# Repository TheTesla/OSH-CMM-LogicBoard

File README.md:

# Coordinate Measurement Arm Logic Board

This logic board implements the main functionality of the 5-dof coordinate measurement arm. The central component is an _Arduino UNO R3_. It reads the rotary encoders out and provides the communication to the host PC and power supply via the USB port. 

The 5 rotary encoders are plugged into the D-Sub-9 socket. The board implements electrical protection circuits, that the _Arduino_ won't be damaged, if voltage is accidentally applied to the encoder connectors. Unfortunatelly, the  USB port can't be protected, because it is directly part of the _Aduino_.

The board also boosts the power supply voltage from the USB port to operate the rotary encoders.

## Implementation

The rotary encoders are powered by a 5 V to 9 V voltage converter, because they need at least 5 V. This lower limit is not maintained by the USB port, which can deliver down to 4.75 V.

Diodes protect the board from excessive positive voltage from the encoder connectors, while 3 transistors protect it from short circuit and negative voltage levels on the encoder supply line. The shunt _R14_ sets the current limit to around 300 mA. At this cuurent level, the b-e-voltage of _Q2_ reaches 660 mV. IN this case _Q2_ starts to disable the output transistor _Q1_. If the output voltage drops down to around 0 V, the diode _D7_ switches the transistor _Q3_ off and so also _Q1_. This reduces the output current in case of short circuit or reverse polarity voltage injection into the power supply output. Diode _D1_ protects _Q3_ against reverse voltage on the output line. 

The _Arduino_ is able to measure the output voltage to report short circuit conditions also as a self test for production end test. 

The encoder data lines are connected via 10k resistors to the _Arduino_ to protect the inputs against excessive voltage from the encoder connector.

The open collector outputs of the encoders need pull-up resistors. These are integrated into the plug of the encoder itself.

If the board is powered up, the power on indicator LED _D10_ shows the correct operation of the voltage converter. If the power supply for the rotary encoders is on, LED _D8_ lights up. For debugging and error indication, the LED _D9_ can be activated by the _Arduino_.

## Associated Projects

The rotary encoders are shipped with open wire ends. A plug has to be attached to this cable. Because there is no electrical protection in the encoder itself. it should be integrated in the plug. This project implements the protection circuit:

* https://github.com/TheTesla/rotary-encoder-protection

## Author/Contact

Stefan Helmert <stefan.helmert@htw-dresden.de>

## Appendix

### Pictures

The following pictures show the rendering of the assembled pcb. The arduino board is not available as 3d model.

### Schematics

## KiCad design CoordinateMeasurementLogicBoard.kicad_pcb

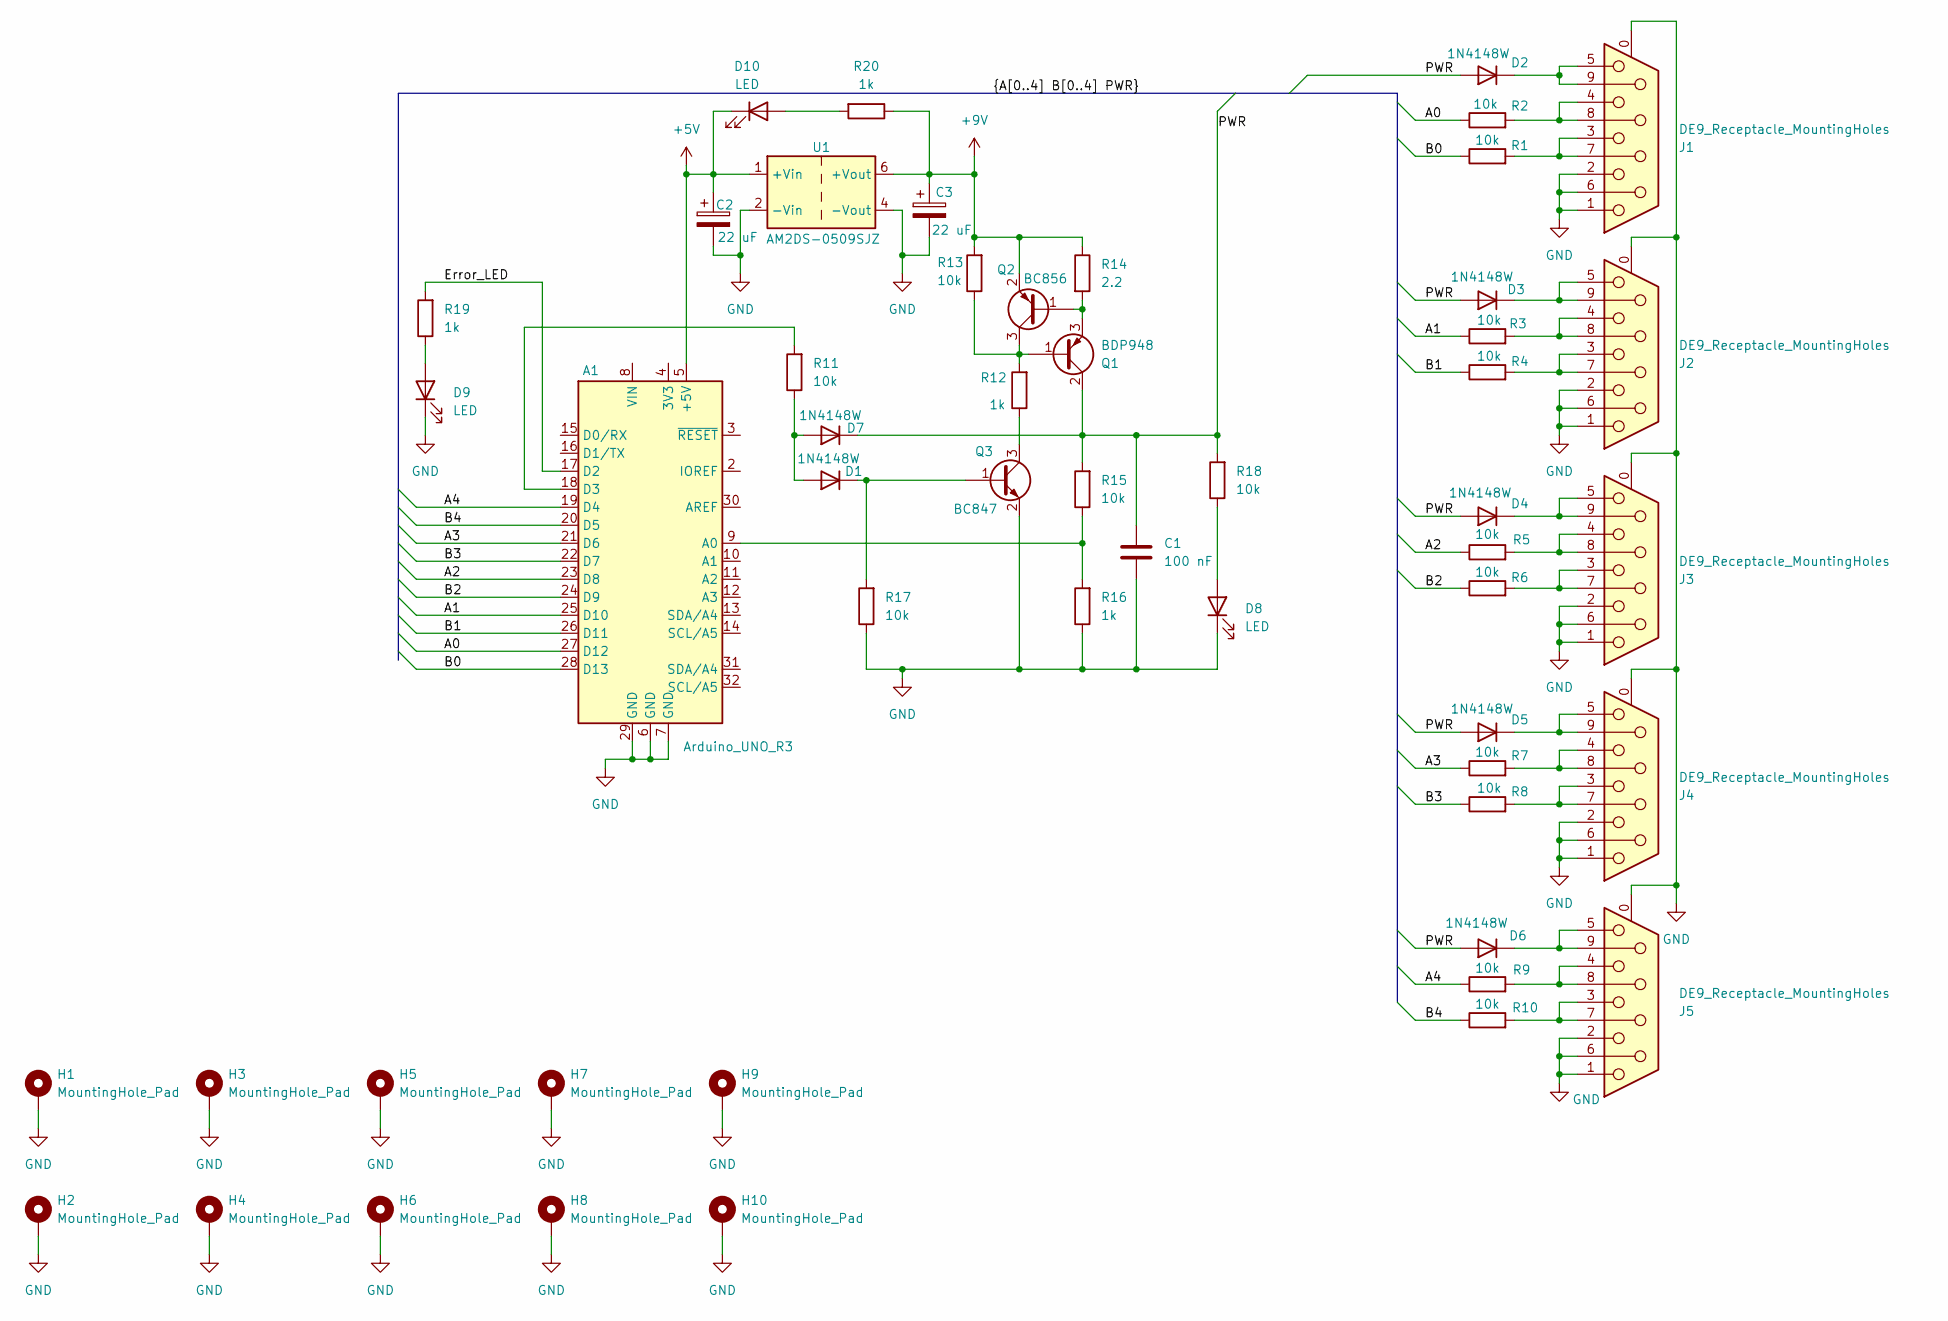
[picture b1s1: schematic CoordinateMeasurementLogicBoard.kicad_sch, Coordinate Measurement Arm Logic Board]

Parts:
A1: Arduino_UNO_R3
C1: 100 nF; C_0805_2012Metric
C2, C3: 22 uF; CP_Radial_D5.0mm_P2.00mm
D1, D2, D3, D4, D5, D6, D7: 1N4148W; D_SOD-123
D8, D9, D10: LED; LED_D5.0mm
H1, H2, H3, H4, H5, H6, H7, H8, H9, H10: MountingHole_Pad; MountingHole_3.2mm_M3_Pad_Via
J1, J2, J3, J4, J5: DE9_Receptacle_MountingHoles; DSUB-9_Female_Horizontal_P2.77x2.84mm_EdgePinOffset4.94mm_H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
Q1: BDP948; SOT-223-3_TabPin2
Q2: BC856; SOT-23
Q3: BC847; SOT-23
R1, R2, R3, R4, R5, R6, R7, R8, R9, R10, R11, R13, R15, R17, R18: 10k; R_0805_2012Metric
R12, R16, R19, R20: 1k; R_0805_2012Metric
R14: 2.2; R_1206_3216Metric
U1: AM2DS-0509SJZ; Converter_DCDC_Aimtec_AM2DS-xxxxSJZ_Single_THT

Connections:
+5V: A1.5 (+5V), C2.1, D10.1 (K), U1.1 (+Vin)
+9V: C3.1, Q2.2 (E), R13.2, R14.1, R20.1, U1.6 (+Vout)
/A0: A1.27 (D12), R2.1
/A1: A1.25 (D10), R3.1
/A2: A1.23 (D8), R5.1
/A3: A1.21 (D6), R7.1
/A4: A1.19 (D4), R9.1
/B0: A1.28 (D13), R1.1
/B1: A1.26 (D11), R4.1
/B2: A1.24 (D9), R6.1
/B3: A1.22 (D7), R8.1
/B4: A1.20 (D5), R10.1
/Error_LED: A1.17 (D2), R19.2
/PWR: C1.1, D2.2 (A), D3.2 (A), D4.2 (A), D5.2 (A), D6.2 (A), D7.1 (K), Q1.2 (C), Q1.4 (C), R15.2, R18.2
GND: A1.6 (GND), A1.7 (GND), A1.29 (GND), C1.2, C2.2, C3.2, D8.1 (K), D9.1 (K), H1.1, H2.1, H3.1, H4.1, H5.1, H6.1, H7.1, H8.1, H9.1, H10.1, J1.0 (PAD), J1.1, J1.2, J1.6, J2.0 (PAD), J2.1, J2.2, J2.6, J3.0 (PAD), J3.1, J3.2, J3.6, J4.0 (PAD), J4.1, J4.2, J4.6, J5.0 (PAD), J5.1, J5.2, J5.6, Q3.2 (E), R16.1, R17.1, U1.2 (-Vin), U1.4 (-Vout)
unnamed: A1.9 (A0), R15.1, R16.2
unnamed: A1.18 (D3), R11.2
unnamed: D1.2 (A), D7.2 (A), R11.1
unnamed: D1.1 (K), Q3.1 (B), R17.2
unnamed: D2.1 (K), J1.5, J1.9
unnamed: D3.1 (K), J2.5, J2.9
unnamed: D4.1 (K), J3.5, J3.9
unnamed: D5.1 (K), J4.5, J4.9
unnamed: D6.1 (K), J5.5, J5.9
unnamed: D8.2 (A), R18.1
unnamed: D9.2 (A), R19.1
unnamed: D10.2 (A), R20.2
unnamed: J1.3, J1.7, R1.2
unnamed: J1.4, J1.8, R2.2
unnamed: J2.3, J2.7, R4.2
unnamed: J2.4, J2.8, R3.2
unnamed: J3.3, J3.7, R6.2
unnamed: J3.4, J3.8, R5.2
unnamed: J4.3, J4.7, R8.2
unnamed: J4.4, J4.8, R7.2
unnamed: J5.3, J5.7, R10.2
unnamed: J5.4, J5.8, R9.2
unnamed: Q1.1 (B), Q2.3 (C), R12.2, R13.1
unnamed: Q1.3 (E), Q2.1 (B), R14.2
unnamed: Q3.3 (C), R12.1

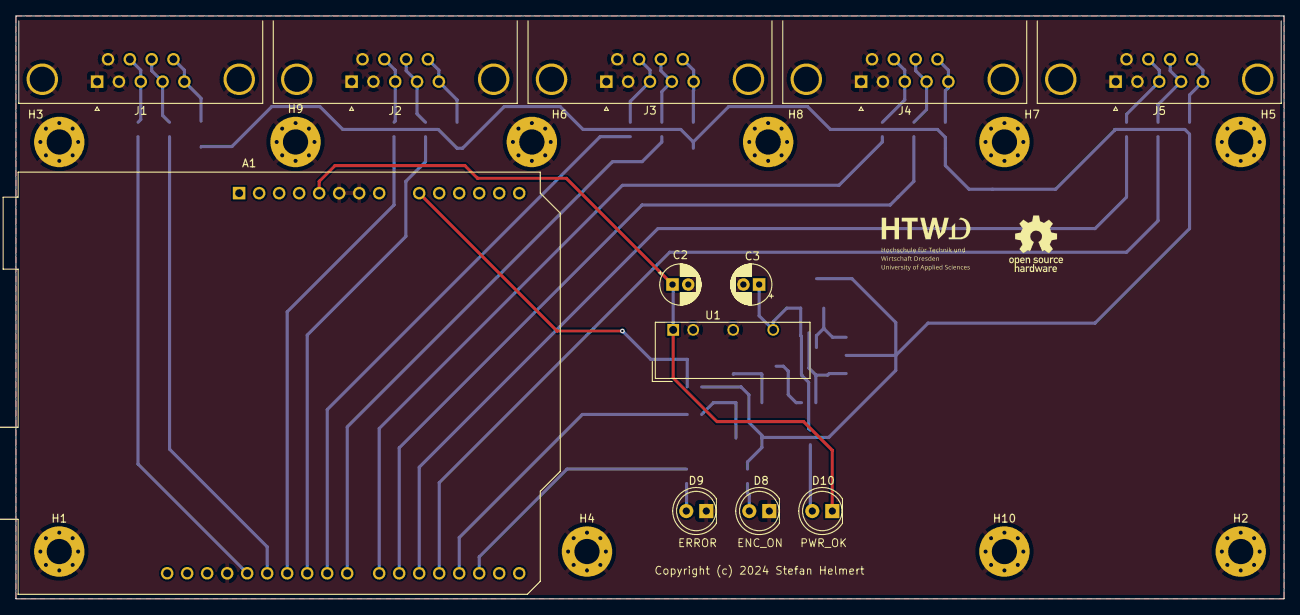
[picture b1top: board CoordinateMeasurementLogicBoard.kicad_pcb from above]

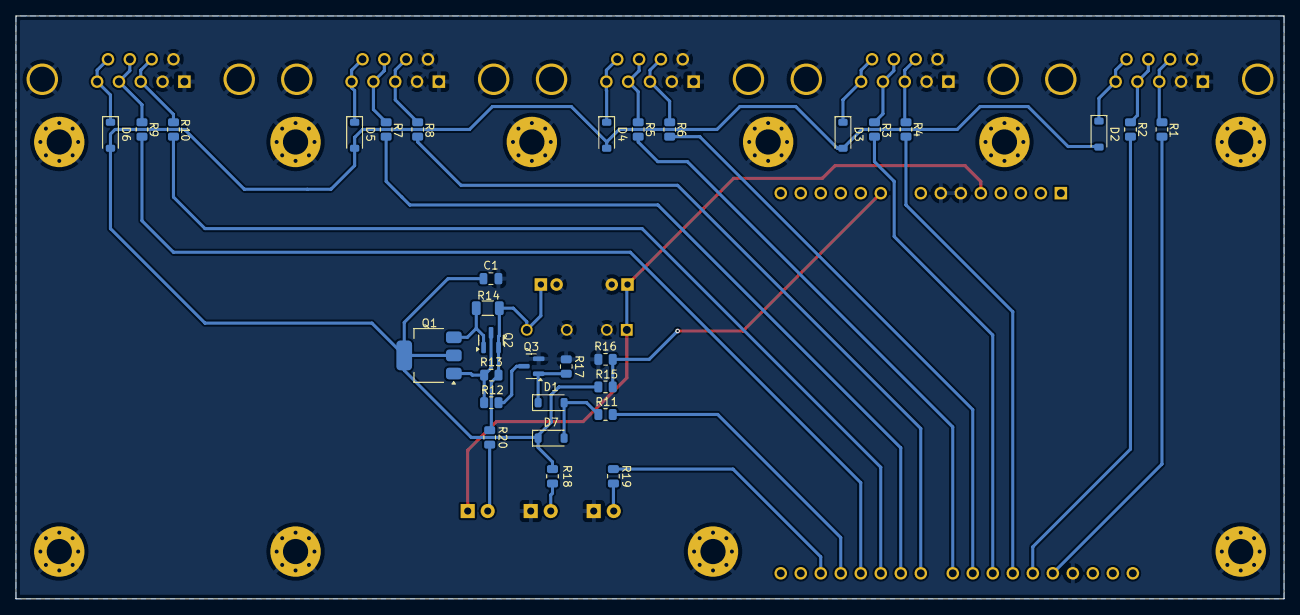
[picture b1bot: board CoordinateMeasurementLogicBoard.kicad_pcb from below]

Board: 2 copper layers, 161.0 x 74.0 mm, 53 parts (31 on the bottom side), 40 nets.

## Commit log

2024-07-11 added symbol, footprint and 3d model for DCDC converter; mostly ready schematic
2024-07-11 one protection circuit for all encoders; todo: select 2.2 ohm shunt, add caps for step up, LEDs
2024-07-12 one protection for all encoders; protection end transistor with 5 W, shunt 0.25 W; caps for dcdc converter
2024-07-17 fix: voltage divider; board nearly ready
2024-07-17 optimized silkscreen; todo: added mounting holes, HTW logo and copyright
2024-07-17 fix: R16 wasn't updated correctly
2024-07-18 ready; mounting holes; cosmetic
2024-07-18 README.md explaining some implementation details
2024-07-19 readme ready
2024-11-25 start case in FreeCAD
2024-11-26 logic board case nearly ready
2024-11-27 PCB fits better
2024-11-28 case top ready
2024-11-28 removed stl
2025-03-14 replaced D-Sub-9 Connector
2025-04-15 repo structure like OSH design guide
2025-04-15 added pictures in README
2025-04-15 added license and okh metadata

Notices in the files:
CoordinateMeasurementLogicBoard.kicad_pcb:
Copyright (c) 2024 Stefan Helmert
